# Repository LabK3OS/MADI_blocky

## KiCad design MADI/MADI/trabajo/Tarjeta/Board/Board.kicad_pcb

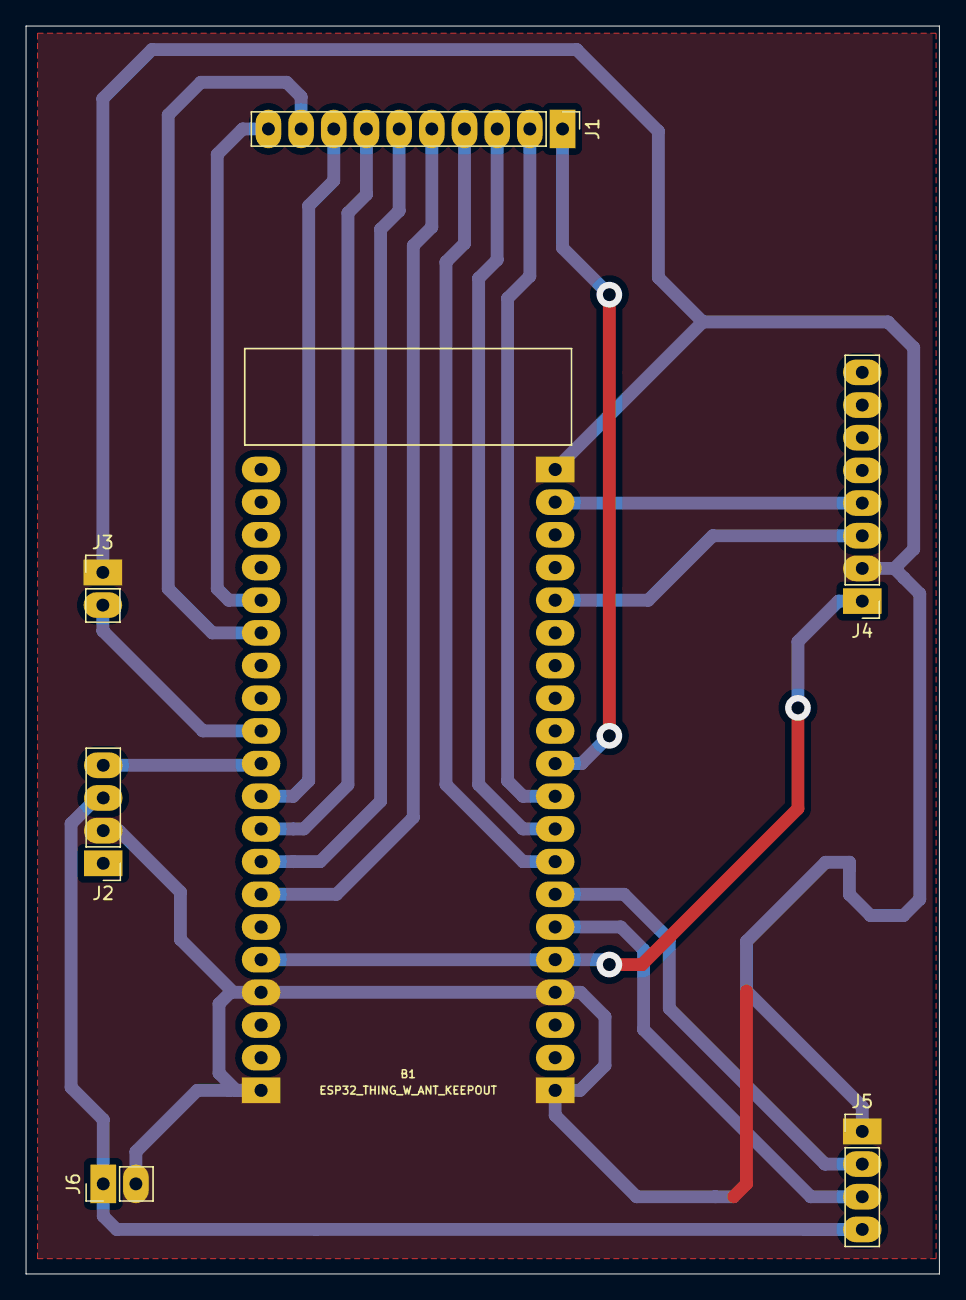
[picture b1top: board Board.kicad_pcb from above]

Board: 2 copper layers, 71.0 x 97.0 mm, 7 parts (0 on the bottom side), 19 nets.

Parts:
B1: ESP32_THING_W_ANT_KEEPOUT; ESP32_THING
J1: Conn_01x10_Female; PinHeader_1x10_P2.54mm_Vertical
J2, J5: Conn_01x04_Female; PinHeader_1x04_P2.54mm_Vertical
J3, J6: Conn_01x02_Female; PinHeader_1x02_P2.54mm_Vertical
J4: Conn_01x08_Female; PinHeader_1x08_P2.54mm_Vertical

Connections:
GND: B1.1, B1.4, B1.21, B1.37, B1.40, J2.2, J3.1, J4.2, J5.1, J6.2
unnamed: B1.7, J1.5
unnamed: B1.8, J1.6
unnamed: B1.9, J1.7
unnamed: B1.10, J1.8
unnamed: B1.11, J2.4
unnamed: B1.12, J3.2
unnamed: B1.15, J1.9
unnamed: B1.16, J1.10
unnamed: B1.22, J4.4
unnamed: B1.25, J4.3
unnamed: B1.30, J1.1
unnamed: B1.31, J1.2
unnamed: B1.32, J1.3
unnamed: B1.33, J1.4
unnamed: B1.34, J5.2
unnamed: B1.35, J5.3
unnamed: B1.5, B1.36, J4.1
unnamed: J2.3, J5.4, J6.1

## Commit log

2019-07-19 add file
    new
2019-07-19 FILE2
    add file2
2019-07-19 add readme
2019-07-19 add file new
2019-07-19 Last Files
2019-07-19 Correction
2019-07-19 erased
2019-07-23 Depuración
2019-07-23 Depuración2
2020-02-24 Se arreglo el fondo y tamaño en codigo Python (Mejor visualización)
2020-02-27 Bloque de sonidos, javascript, y python para colocar
2020-02-27 Sonidos w4a y music maker
2020-02-29 La depuracion no funciono, toca volver a dejar los archivos originales
2020-02-29 Esa parte comentada quien sabe que era ¿?
2020-02-29 Prueba
2020-02-29 Arreglo
2020-02-29 arreglo2
2020-02-29 Arreglo?
2020-02-29 no sé si ya funciona
2020-02-29 ya funcionan los sonidos!!!!
2020-03-02 Arreglos Varios
2020-03-02 Se le puso todas las teclas del piano, pero falta arreglar la reproduccion de sonidos
2020-03-03 Recortaron audios y se arreglo la reproduccion?, falta agregarle retrasos?
2020-03-06 Se arreglo el sonido a medias, pero falta compilarlo ya que le agregue Tempo
2020-03-06 Falta compilarlo, y falta agregar la opcion de reproduccion seguida
2020-03-06 NO me acuerdo que hice
2020-03-15 Cambie el bloque
2020-03-15 lo arregle?
2020-03-15 arreglado
2020-03-16 Puse tiempo de reproduccion y combinacion de sonidos y borré anteriores pruebas
2020-03-16 Falta compilar, pero ya agregue esperas en segundos, milisegundos y microsegundos
2020-03-17 Comprimido
2020-03-17 Arregle el error de value_esperar_ms
2020-04-04 NUevos bloques sensor ULtrasonico
2020-04-04 NUevos bloques para mpu6050, toca arreglar GPIO y Touch
2020-04-04 Arreglos
2020-04-04 CAmbios
2020-04-04 Se configuraron pines para el ESP32
2020-04-06 Añade el Import a cualquier libreria sí esta falta
2020-04-07 Blocks ADC
2020-04-12 GPIO UPGRADE
2020-04-15 Sistema de comprobacion de pines no repetidos
2020-04-15 Comprobador funcionando
2020-04-15 Imagen con el PinOut de la ESP32 para guiarse con la configuracion de los pines
2020-04-19 docx
2020-04-22 Falta compilar
2020-04-22 no sé
2020-04-25 nuevos sonidos?
2020-04-25 audio mejoradisimo
2020-04-25 Animacion de teclado, falta compilar
2020-04-25 COmpilado
2020-04-26 servira?
2020-04-26 tratando de animar :'(
2020-04-26 alumbrado de bloques
2020-04-26 Piano con notas
2020-04-27 creo saber como animar
2020-04-28 neopixel
2020-04-29 adelanto de tesis
2020-04-29 NeoPixel, nuevas funciones pero falta compilar
2020-04-30 no funciona neopixel
2020-04-30 Falta compilar y probar a ver que :S
2020-04-30 Ya funciona el NeoPixel
2020-05-01 ya arregle neo pixel
2020-05-01 color arreglado pero no funciona el aleatorio
2020-05-02 Se configuraron sombras y bloques predeterminados para mejor comprencion
2020-05-02 se depuro algo
2020-05-06 Se le agregaron Timers
2020-05-07 arregle timer
2020-05-07 Prueba de timer y Neopixel, reloj analogo
2020-05-07 falta cargar bloques :S
2020-05-07 funciona guardado y carga de bloques
2020-05-08 timer funciona bien
2020-05-08 libreria random?
2020-05-08 otra parte de random pero no sé cual sirve
2020-05-08 compile con la nueva libreria pero no la he probado...
2020-05-09 YA FUNCIONA LA MUSICA POR HARDWARE e hice cambios al bloque para ajustarse al hardware
2020-05-10 arreglos grandes en el sonido por hardware, y cambios en el codigo, comienza pruebas de sensores y sus librerias
2020-05-10 pruebas
2020-05-10 arreglos en rtc
2020-05-11 separacion de arreglos de rtc y mpu, y agregar DAC para reproduccion de tonos combinados (Sin probar)
2020-05-11 ajustes en el color para todos
2020-05-11 no sirvió, siguiente paso, hacer el servo motor?
2020-05-13 arreglos pequeños
2020-05-13 RTC desde un servidor
2020-05-14 rtc online
2020-05-14 RTC online funciona
2020-05-16 Board
2020-05-16 le baje una octava
2020-05-16 ghgf
2020-05-17 corazon encantado <3
2020-05-18 Arreglos en la tesis :)
2020-05-18 quite algo :D
2020-05-18 hasdha
2020-05-19 libreria para sensor de color :O
2020-05-20 nadfa
2020-05-20 dac esp32
2020-05-20 DAC importante, pero nada mas se puede con la ESP32
2020-05-20 Modificando el tipo de onda se pueden obtener diferentes instrumentos musicales :)
2020-05-21 diferentes instrumentos
2020-05-22 Funciones
2020-05-23 arreglos de sonido
2020-05-26 datos de la PCB
2020-05-26 cosas mejoradas del documento
2020-06-01 nasd
2020-06-02 GENERADOR DE ONDA
2020-06-02 mario
2020-06-02 arreglos en random
2020-06-03 arreglos ya que no funciono el DAC así que quedo con PWM
2020-06-03 touch funciona bien
2020-06-08 adelantos
2020-06-08 tesis
2020-07-04 hola
    Hola
2020-07-04 C:\U
2020-07-06 Update tesis_f.docx
    Terminado?
2020-07-06 Update code.js
    arreglo
2020-07-06 Update code.js
    prueba
2020-07-06 Update tesis_f.docx
    tesis arreglada
2020-07-08 Update tesis_f.docx
    arreglos creo
2020-07-08 Create tesis_f (1).docx
    tesis
2020-07-13 Update tesis.docx
    arreglos finales?
2020-07-18 arreglos finales
2020-07-27 presentacion
2020-09-03 Bump google-closure-library from 20180805.0.0 to 20200830.0.0
    Bumps [google-closure-library](https://github.com/google/closure-library) from 20180805.0.0 to 20200830.0.0.
    - [Release notes](https://github.com/google/closure-library/releases)
    - [Commits](https://github.com/google/closure-library/compare/v20180805...v20200830)
2021-02-13 Cambio de sonido natural
